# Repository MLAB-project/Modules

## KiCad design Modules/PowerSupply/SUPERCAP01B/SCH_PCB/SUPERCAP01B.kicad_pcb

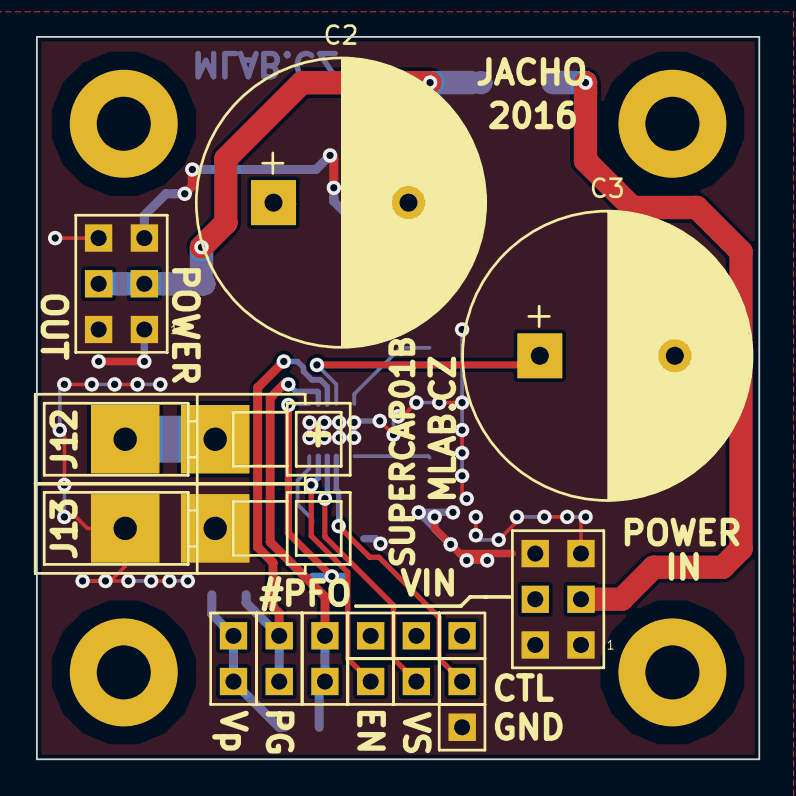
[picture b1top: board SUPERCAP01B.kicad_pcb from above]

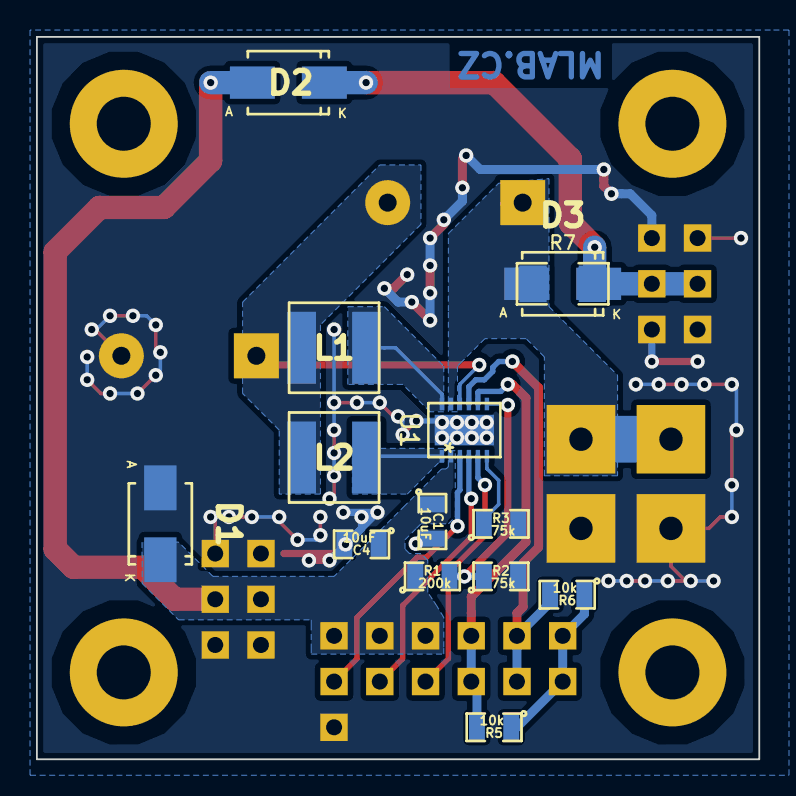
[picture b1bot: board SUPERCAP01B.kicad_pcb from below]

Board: 2 copper layers, 40.1 x 40.1 mm, 34 parts (14 on the bottom side), 15 nets.

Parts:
C1, C4: 10uF; SMD-0805
C2, C3: 22F; C_Radial_D16_L25_P7.5
D1: M4; SMA_Standard
D2, D3: 15MQ040N; Diode-SMA_Standard
J1, J11: JUMP_3X2; Straight_2x03
J2, J3, J4, J5, J6, J7, J8: CONN1_1; Straight_1x01
J9, J10, J14: JUMP_2x1; Straight_2x01
J12, J13: CONN1_1; WAGO256
L1, L2: DJNR5040-3R3-S; DJNR5040
M1, M2, M3, M4: HOLE; MountingHole_3mm
R1: 200k; SMD-0805
R2, R3: 75k; SMD-0805
R5, R6: 10k; SMD-0805
R7: 0R; SMD-1206
U1: LTC3625; DFN-12-1EP_3x4mm_Pitch0.5mm

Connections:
/#PFO: J9.1, J9.2, R5.2, U1.8
/CTL: J3.1, U1.3
/EN: J6.1, U1.5
/OUT: C2.1, D3.2, J12.1, R7.2, U1.11
/OUT2: D2.1, D3.1, J11.3, J11.4, R7.1
/PG: J10.1, J10.2, R6.2, U1.9
/VIN: C1.1, C4.1, D1.1, D2.2, J1.3, J1.4, J2.1, J5.1, J7.1, R1.1, U1.2
/VSEL: J8.1, U1.4
/Vpull-up: J14.1, J14.2, R5.1, R6.1
GND: C1.2, C3.2, C4.2, D1.2, J1.1, J1.2, J1.5, J1.6, J4.1, J11.1, J11.2, J11.5, J11.6, J13.1, R2.2, R3.2, U1.13
unnamed: C2.2, C3.1, L1.2, L2.2, U1.10
unnamed: L1.1, U1.12
unnamed: L2.1, U1.1
unnamed: R1.2, R2.1, U1.7
unnamed: R3.1, U1.6

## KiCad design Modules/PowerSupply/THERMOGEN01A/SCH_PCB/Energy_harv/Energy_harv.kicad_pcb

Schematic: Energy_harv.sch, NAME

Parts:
C1, C10: 47uF; TantalC_SizeC_Reflow
C2, C4: 1nF; SMD-0805
C3, C5: 470pF; SMD-0805
C6: 1uF; SMD-0805
C7: 2,2uF; SMD-0805
C8: 470uF; TantalC_SizeD_Reflow
C9: 1-10F; Straight_1x02
J1, J2: JUMP1X3; Straight_1x03
J3, J4: JUMP1X2; Straight_1x02
J5, J6: JUMP2X3; Straight_2x03
M1, M2, M3, M4: HOLE; MountingHole_3mm
P1, P2, P3, P4: WAGO256
T1, T2: Step-Up_TRANSFO; Step-Up_TRANSF
U1: THERM_GEN; Straight_1x02
U2: LTC3109GN; SSOP-20

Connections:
/C+: C9.1, P4.1, U2.3 (VSTORE)
/PGOOD: J4.1, J4.2, U2.8 (PGOOD)
/T+: C1.1, P1.1, T1.1 (AA), U1.2, U2.15 (V_INB)
/T-: C1.2, P2.1, T2.1 (AA), U1.1, U2.16 (V_INA)
/VAUX: C6.1, J1.3, J2.3, U2.4 (VAUX)
/VOUT2_EN: J3.1, J3.2, U2.7 (V_OUT2_EN)
/VS1: J1.2, U2.1 (VS1)
/VS2: J2.2, U2.2 (VS2)
/V_OUT: C8.1, J6.3, J6.4, U2.5 (V_OUT)
/V_OUT2: C10.1, J5.3, J5.4, U2.6 (V_OUT2)
GND: C6.2, C7.2, C8.2, C9.2, C10.2, J1.1, J2.1, J5.1, J5.2, J5.5, J5.6, J6.1, J6.2, J6.5, J6.6, P3.1, T1.3 (SA), T2.3 (SA), U2.10 (GND), U2.13 (GND), U2.18 (GND)
unnamed: C2.1, U2.20 (C1A)
unnamed: C2.2, C3.2, T1.4 (SB)
unnamed: C3.1, U2.19 (C2A)
unnamed: C4.1, U2.11 (C1B)
unnamed: C4.2, C5.2, T2.4 (SB)
unnamed: C5.1, U2.12 (C2B)
unnamed: C7.1, U2.9 (VLDO)
unnamed: T1.2 (AB), U2.17 (SWA)
unnamed: T2.2 (AB), U2.14 (SWB)

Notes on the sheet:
V_out2
V_out

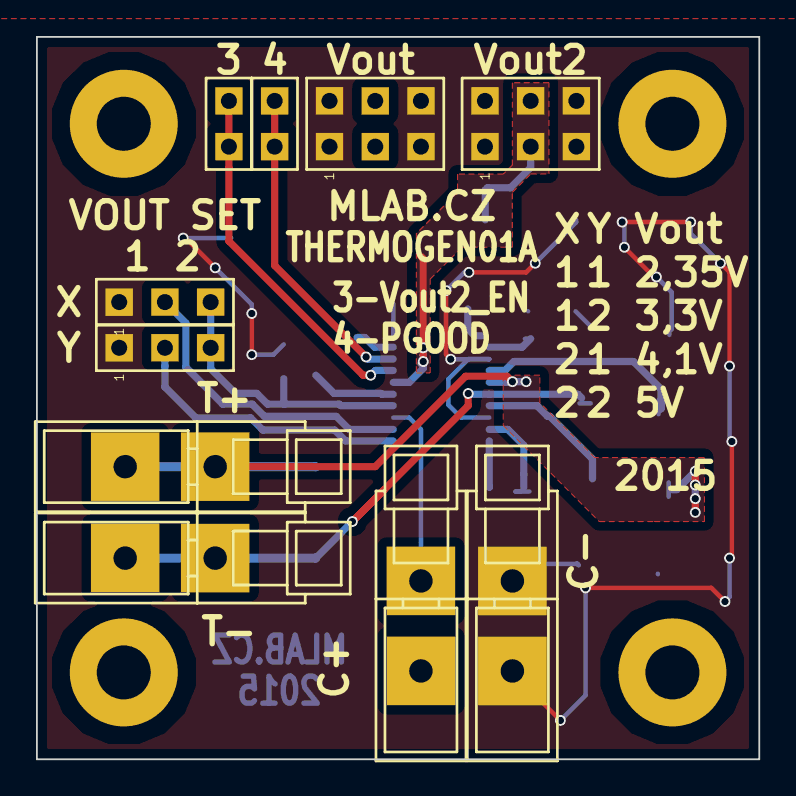
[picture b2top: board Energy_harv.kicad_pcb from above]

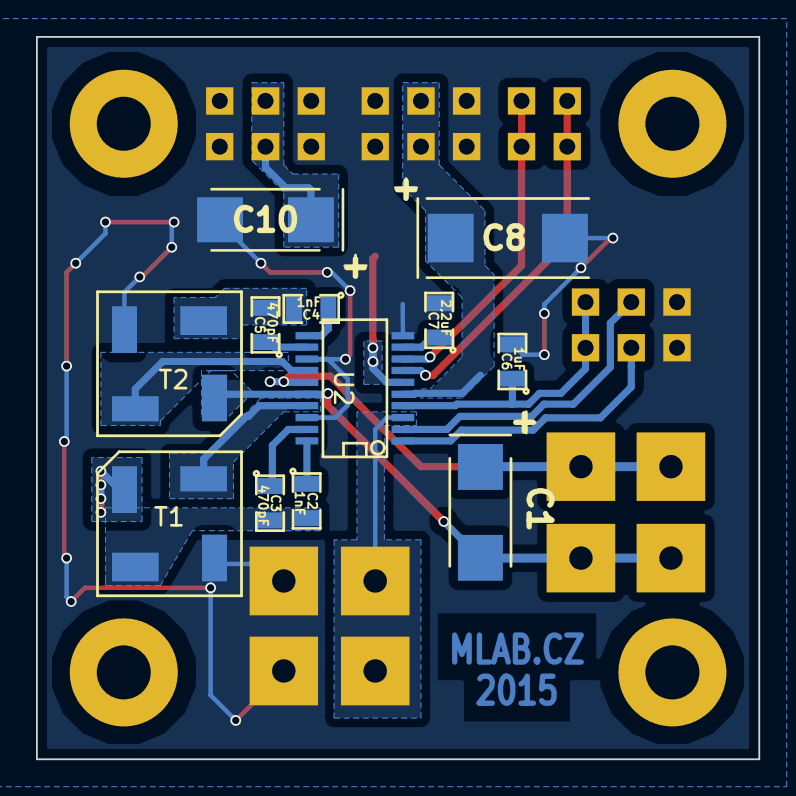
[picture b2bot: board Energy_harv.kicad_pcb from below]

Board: 2 copper layers, 40.1 x 40.1 mm, 26 parts (12 on the bottom side), 20 nets.

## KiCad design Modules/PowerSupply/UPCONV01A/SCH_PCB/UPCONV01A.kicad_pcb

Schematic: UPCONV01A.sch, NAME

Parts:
C1: 470uF; TantalC_SizeD_Reflow
C2, C6: 100nF; SMD-0805
C3: 10uF/16V; SMD-0805
C5, C7: 220uF; TantalC_SizeD_Reflow
C9: 10uF; SMD-0805
C10: 2.2nF; SMD-0805
C11: 47pF; SMD-0805
C12: 10nF; SMD-0805
C13: 100pF; SMD-0805
C14: 10uF/25V; SMD-0805
C15: 470pF; SMD-0805
C21: 470uF/35V; C_Radial_D10_L13_P5
D1: M4; Diode-SMA_Standard
D2, D3: STPS340U; Diode-SMB_Standard
J1, J2, J3, J7, J8, J9, J10, J11, J12: JUMP_2x1; Straight_1x02
J4, J5, J6: JUMP2_2x1; Straight_1x02
L1: DE1207-10, EPCOS B82477G4682M; DE1205-10
L2: BLM21PG300SN1; SMD-0805
M1, M2, M3, M4: HOLE; MountingHole_3mm
P1, P2, P3, P4: WAGO256
R1: 51k; SMD-0805
R2, R4: 10k; SMD-0805
R3: 84k5; SMD-0805
R5: 28k7; SMD-0805
R6: -; SMD-0805
R7: 499R; SMD-0805
U1: PAM2423; SOP-8_EP_3.9x4.9mm_Pitch1.27mm

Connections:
/5V: J5.1, R5.1
/12V: J4.1, R4.1
/ADJ: J6.1, R6.1
/EN: J2.1, J2.2, R2.2, U1.3 (EN)
/Vout: C5.1, C7.1, C13.1, C14.1, C21.1, D2.1 (K), D3.1 (K), L2.1, P3.1, R7.1
GND: C1.2, C2.2, C3.2, C5.2, C6.2, C7.2, C9.2, C10.2, C11.2, C12.2, C14.2, C15.2, C21.2, D1.2 (A), J1.1, J1.2, J3.1, J3.2, J7.1, J7.2, J10.1, J10.2, J12.1, J12.2, P2.1, P4.1, R4.2, R5.2, R6.2, U1.1 (PGND), U1.5 (AGND), U1.9 (GND)
unnamed: C6.1, J8.1, J8.2, J9.1, J9.2, L2.2
unnamed: C10.1, R1.2
unnamed: C11.1, R1.1, U1.4 (COMP)
unnamed: C12.1, U1.7 (SS)
unnamed: C13.2, C15.1, J4.2, J5.2, J6.2, R3.2, U1.6 (FB)
unnamed: D2.2 (A), D3.2 (A), L1.2, U1.8 (SW)
unnamed: R3.1, R7.2
VCC: C1.1, C2.1, C3.1, C9.1, D1.1 (K), J11.1, J11.2, L1.1, P1.1, R2.1, U1.2 (VIN)

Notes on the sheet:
POWER INPUT
MOUNTING HOLES
POWER OUT

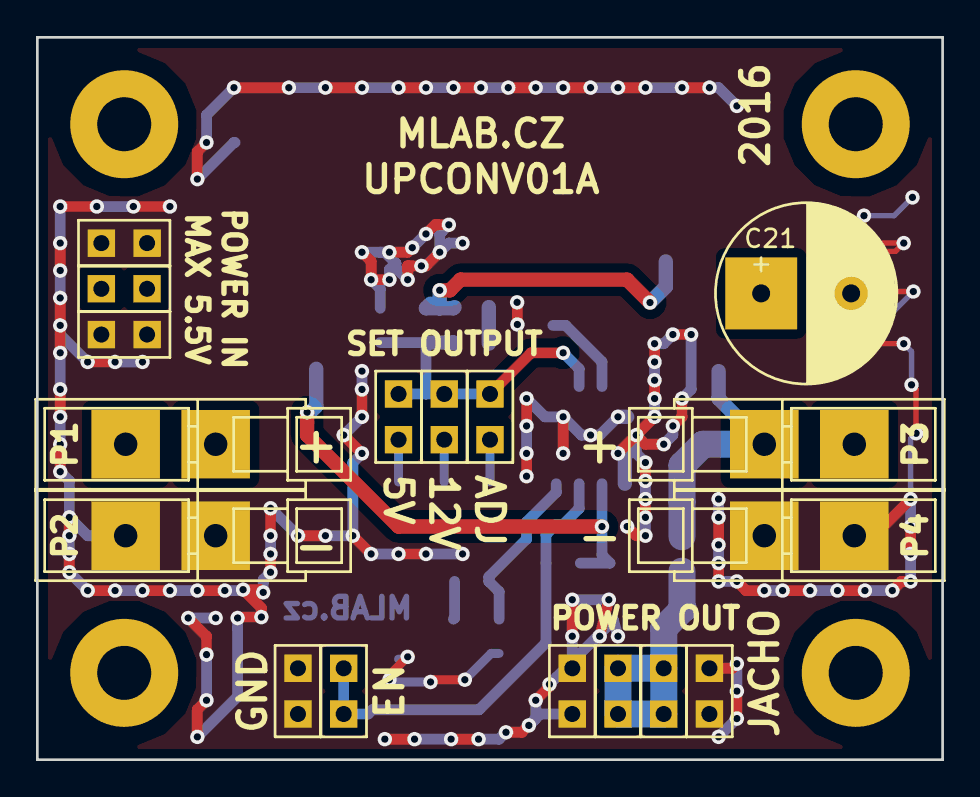
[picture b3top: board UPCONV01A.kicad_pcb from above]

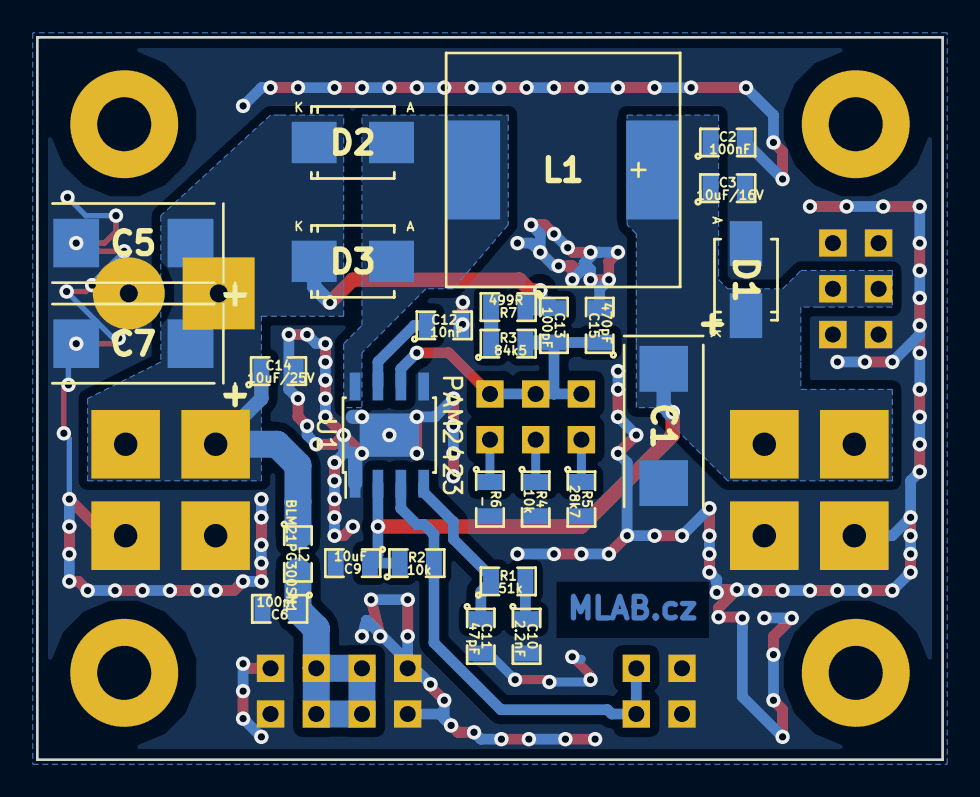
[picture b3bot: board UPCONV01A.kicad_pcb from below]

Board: 2 copper layers, 50.3 x 40.1 mm, 47 parts (26 on the bottom side), 14 nets.

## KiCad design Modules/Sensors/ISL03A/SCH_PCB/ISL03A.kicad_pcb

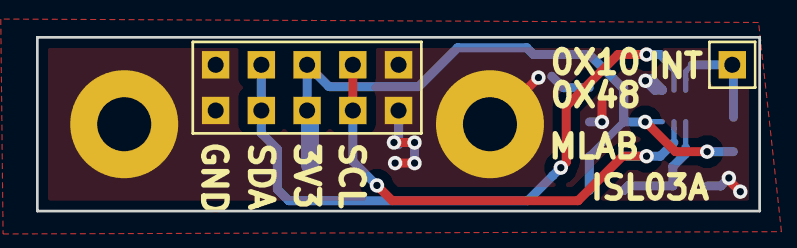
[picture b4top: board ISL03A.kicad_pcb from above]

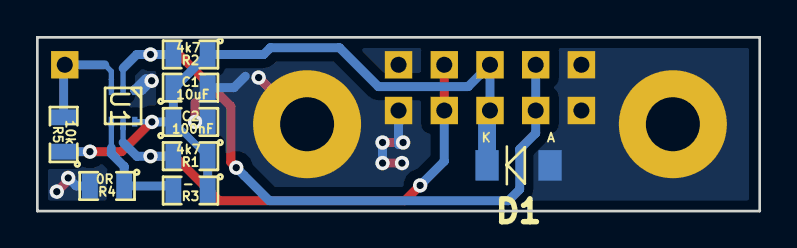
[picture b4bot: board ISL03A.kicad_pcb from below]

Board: 2 copper layers, 40.1 x 9.7 mm, 13 parts (9 on the bottom side), 6 nets.

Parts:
C1: 10uF; SMD-0805
C2: 100nF; SMD-0805
D1: BZV55C-3,6V; Diode-MiniMELF_Standard
J1: JUMP_5X2; Straight_2x05
J2: CONN1_1; Straight_1x01
M1, M2: HOLE; MountingHole_3mm
R1, R2: 4k7; SMD-0805
R3: -; SMD-0805
R4: 0R; SMD-0805
R5: 10k; SMD-0805
U1: VEML6030

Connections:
+3V3: C1.1, C2.1, D1.2, J1.5, J1.6, R1.1, R2.1, R3.1, R5.1, U1.6
/INT: J2.1, R5.2, U1.3
/SCL: J1.7, J1.8, R1.2, U1.5
/SDA: J1.3, J1.4, R2.2, U1.2
GND: C1.2, C2.2, D1.1, J1.1, J1.2, J1.9, J1.10, M1.1, M2.1, R4.2, U1.1
unnamed: R3.2, R4.1, U1.4

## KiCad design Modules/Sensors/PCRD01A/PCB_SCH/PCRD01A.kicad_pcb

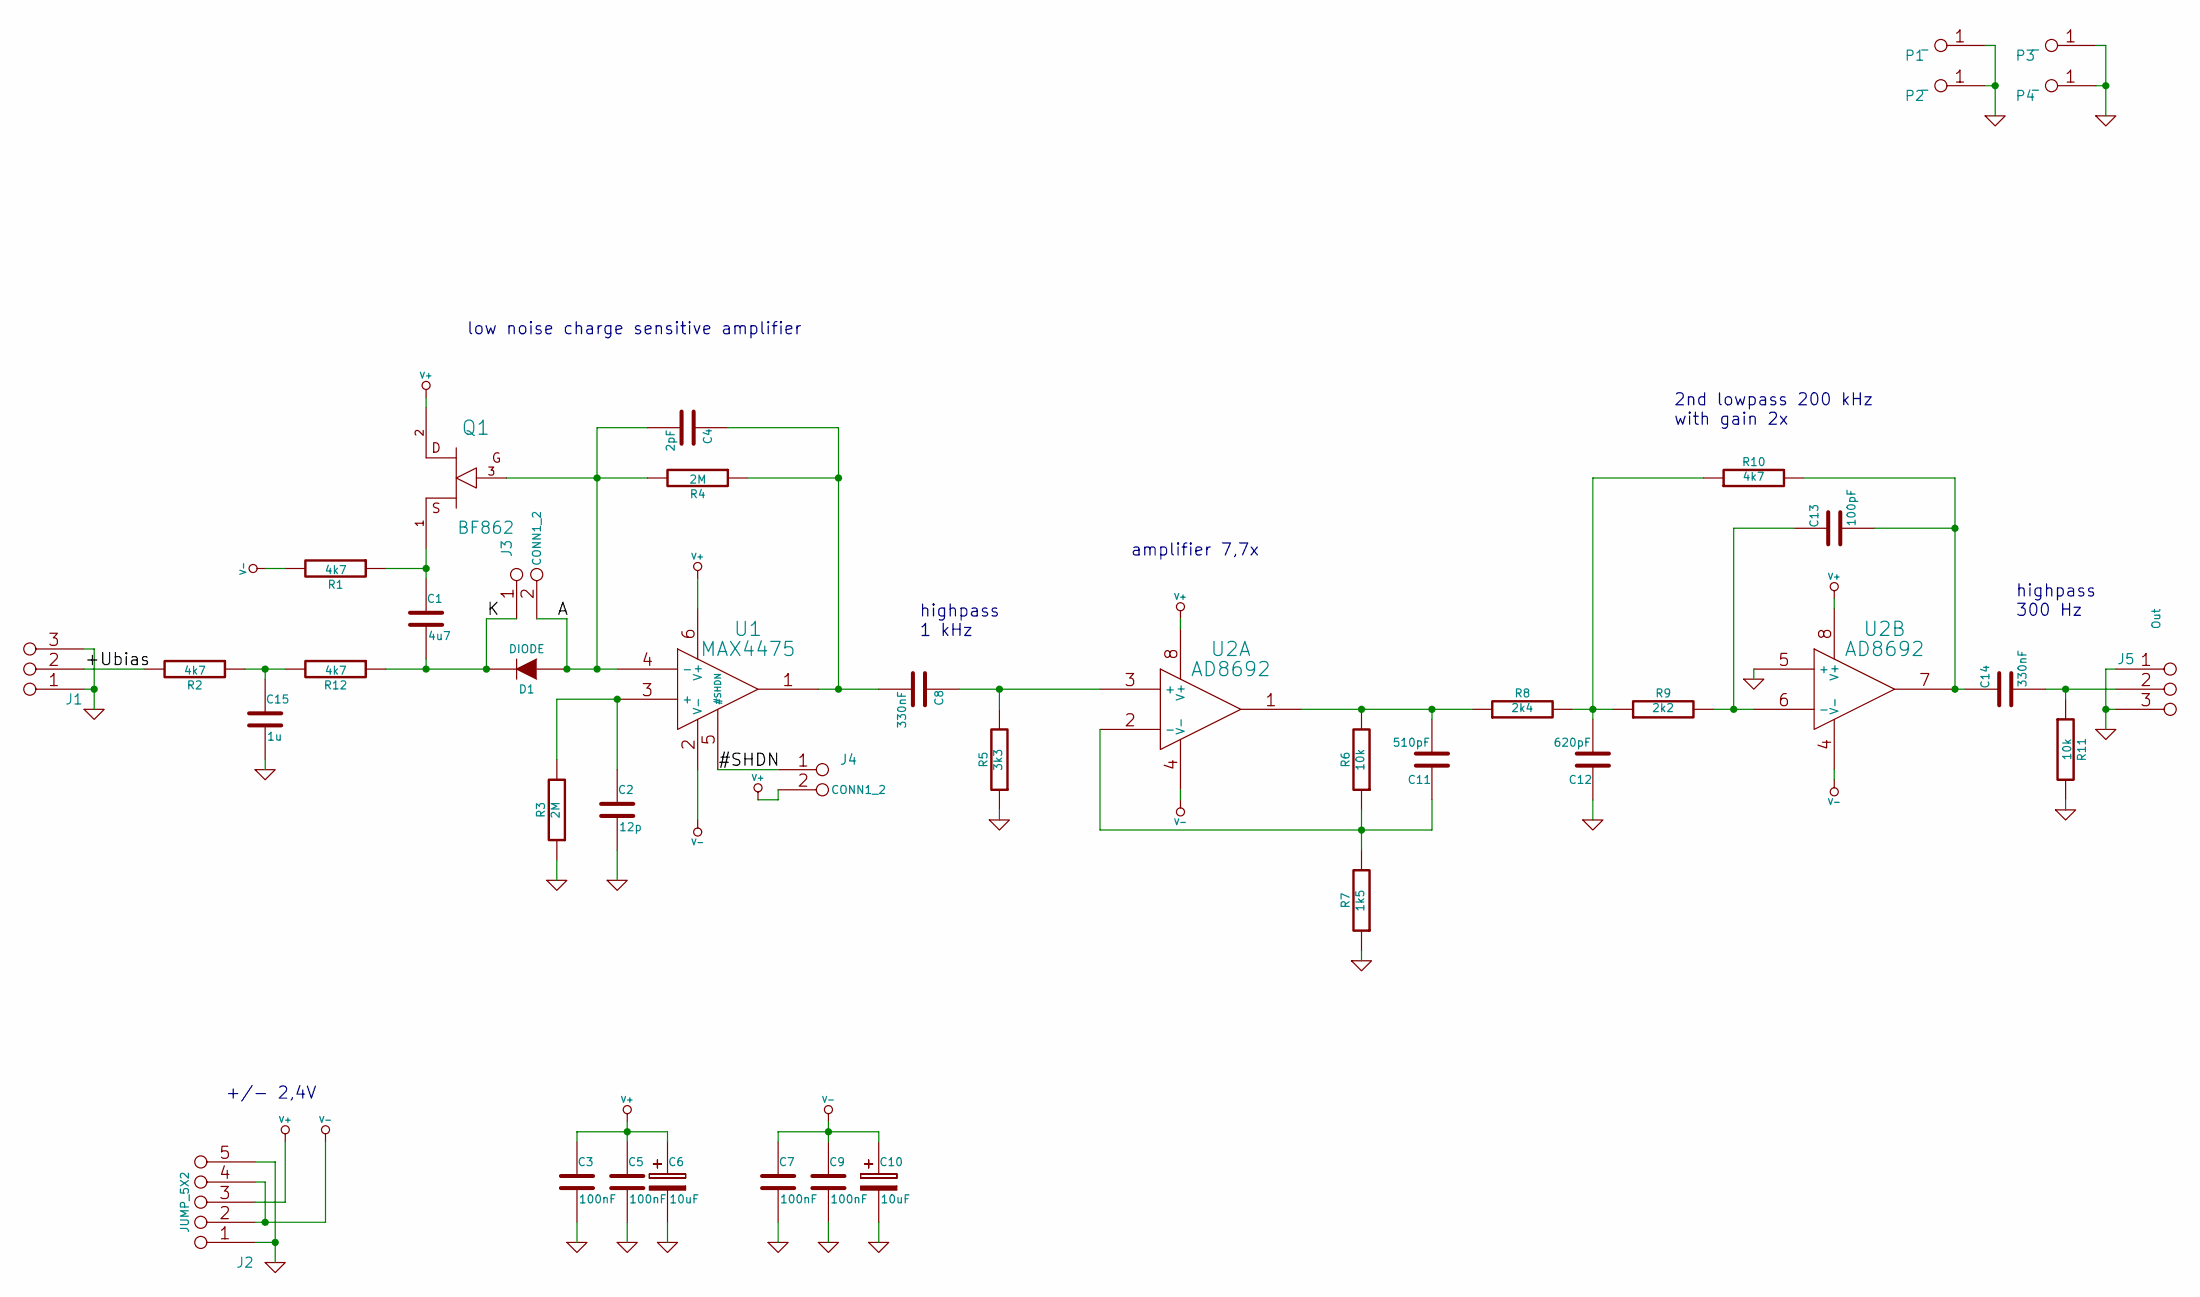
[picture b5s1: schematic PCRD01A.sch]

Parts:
C1: 4u7; SMD-0805
C2: 12p; SMD-0805
C3, C5, C7, C9: 100nF; SMD-0805
C4: 2pF; SMD-0805
C6, C10: 10uF; SMD-0805
C8, C14: 330nF; SMD-0805
C11: 510pF; SMD-0805
C12: 620pF; SMD-0805
C13: 100pF; SMD-0805
C15: 1u; SMD-0805
D1: DIODE
J1: JUMP_3X2; Pin_Header_Straight_2x03
J2: JUMP_5X2; Pin_Header_Straight_2x05
J3: CONN1_2; CONN_3_2
J4: CONN1_2; Pin_Header_Straight_1x02
J5: Out; Pin_Header_Straight_2x03
P1, P2, P3, P4: _; MountingHole_3mm
Q1: BF862; SOT-23
R1, R2, R10, R12: 4k7; SMD-0805
R3, R4: 2M; SMD-0805
R5: 3k3; SMD-0805
R6, R11: 10k; SMD-0805
R7: 1k5; SMD-0805
R8: 2k4; SMD-0805
R9: 2k2; SMD-0805
U1: MAX4475; SOT-23-6
U2: AD8692; SOIC-8-N

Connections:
/#SHDN: J4.1, U1.5 (#SHDN)
/+Ubias: J1.2 (1), J1.5, R2.2
/A: C4.2, D1.1 (A), J3.2 (PM), Q1.3 (G), R4.2, U1.4 (-)
/K: C1.2, D1.2 (K), J3.1, R12.1
GND: C2.2, C3.2, C5.2, C6.2, C7.2, C9.2, C10.2, C12.1, C15.2, J1.1, J1.3, J1.4, J1.6, J2.1, J2.5, J2.6, J2.10, J5.1, J5.3, J5.4, J5.6, P1.1, P2.1, P3.1, P4.1, R3.1, R5.1, R7.1, R11.2, U2.5 (+)
unnamed: C1.1, Q1.1 (S), R1.1
unnamed: C2.1, R3.2, U1.3 (+)
unnamed: C4.1, C8.2, R4.1, U1.1
unnamed: C8.1, R5.2, U2.3 (+)
unnamed: C11.1, R6.1, R7.2, U2.2 (-)
unnamed: C11.2, R6.2, R8.1, U2.1
unnamed: C12.2, R8.2, R9.1, R10.1
unnamed: C13.1, R9.2, U2.6 (-)
unnamed: C13.2, C14.1, R10.2, U2.7
unnamed: C14.2, J5.2 (1), J5.5, R11.1
unnamed: C15.1, R2.1, R12.2
V+: C3.1, C5.1, C6.1, J2.3, J2.8, J4.2 (PM), Q1.2 (D), U1.6 (V+), U2.8 (V+)
V-: C7.1, C9.1, C10.1, J2.2, J2.4, J2.7, J2.9, R1.2, U1.2 (V-), U2.4 (V-)

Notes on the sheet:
low noise charge sensitive amplifier
highpass 1 kHz
amplifier 7,7x
2nd lowpass 200 kHz with gain 2x
highpass 300 Hz
+/- 2,4V

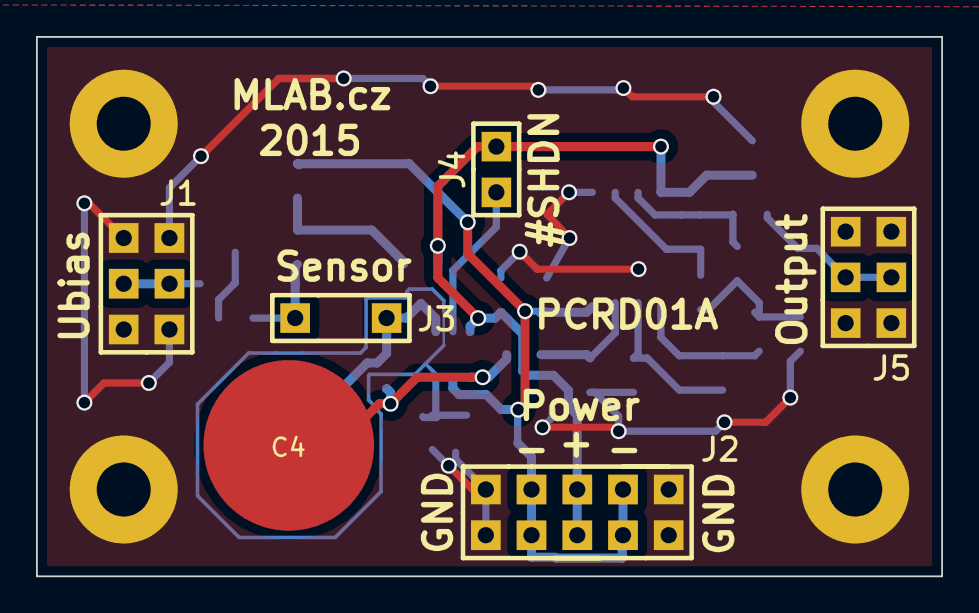
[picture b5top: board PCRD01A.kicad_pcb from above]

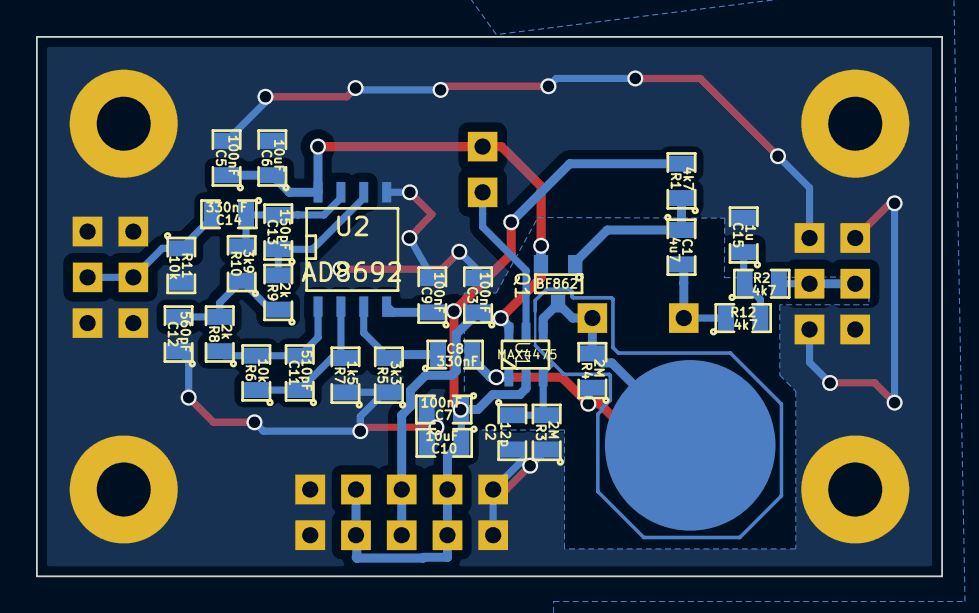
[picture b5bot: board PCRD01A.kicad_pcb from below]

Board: 2 copper layers, 50.3 x 30.0 mm, 39 parts (29 on the bottom side), 18 nets.

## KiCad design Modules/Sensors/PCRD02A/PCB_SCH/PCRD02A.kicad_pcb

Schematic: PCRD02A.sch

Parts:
C1, C2: 100nF; SMD-0805
C3, C4, C9, C10, C11: 100n; SMD-0805
C5, C8: 2pF; C2pF
C13, C17: 330nF; SMD-0805
C14: 510pF; SMD-0805
C15: 240pF; SMD-0805
C16: 180pF; SMD-0805
D1: DIODE
J1: CONN1_2; CONN_3_2
J2: JUMP_3X2; Pin_Header_Straight_2x03
J3: JUMP_5X2; Pin_Header_Straight_2x05
J4: Out; Pin_Header_Straight_2x03
P1, P2, P3, P4: _; MountingHole_3mm
Q1: BF862; SOT-23
R1, R2: 4M7; SMD-0805
R3, R4, R5, R6: R; SMD-0805
R7: 2M; SMD-0805
R8: 3k3; SMD-0805
R9, R15: 10k; SMD-0805
R10: 1k5; SMD-0805
R11: 3k9; SMD-0805
R12, R13, R14: 2k4; SMD-0805
U1: AD8691; tsot-5
U2: AD8692; SOIC-8-N

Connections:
GND: C1.2, C3.2, C4.2, C9.2, C10.2, C11.2, C15.2, D1.1 (A), J1.1, J2.1, J2.3, J2.4, J2.6, J3.1, J3.5, J3.6, J3.10, J4.1, J4.3, J4.4, J4.6, P1.1, P2.1, P3.1, P4.1, R8.2, R10.2, R13.2, R15.2
unnamed: C1.1, R1.2, R2.1
unnamed: C2.1, C8.2, Q1.3 (G), R7.2
unnamed: C2.2, D1.2 (K), J1.2 (PM), R2.2
unnamed: C5.1, R5.2, R6.1, U1.4 (-)
unnamed: C13.1, R8.1, U2.3
unnamed: C8.1, C13.2, R7.1, U1.1
unnamed: C14.1, R9.2, R10.1, U2.2
unnamed: C14.2, R9.1, R11.2, U2.1
unnamed: C15.1, R12.1, U2.5
unnamed: C16.1, C17.2, R14.1, U2.7
unnamed: C16.2, R11.1, R12.2
unnamed: C17.1, J4.2 (1), J4.5, R15.1
unnamed: J2.2 (1), J2.5, R1.1
unnamed: Q1.2 (D), R4.2, U1.3 (+)
unnamed: R3.2, R4.1, R5.1
unnamed: R13.1, R14.2, U2.6
V+: C3.1, C4.1, J3.3, J3.8, R3.1, U1.5 (V+), U2.8
V-: C5.2, C9.1, C10.1, C11.1, J3.2, J3.4, J3.7, J3.9, Q1.1 (S), R6.2, U1.2 (V-), U2.4

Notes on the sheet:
low noise charge sensitive amplifier
highpass 1 kHz
amplifier 7,7x
2nd lowpass 200kHz with gain 2x
highpass 300 Hz
+/- 2,4 V

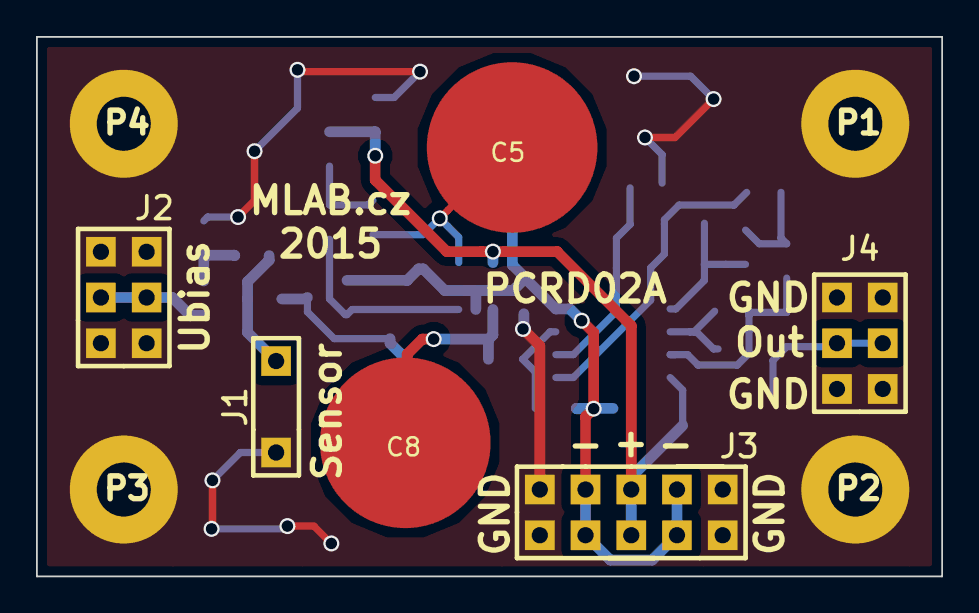
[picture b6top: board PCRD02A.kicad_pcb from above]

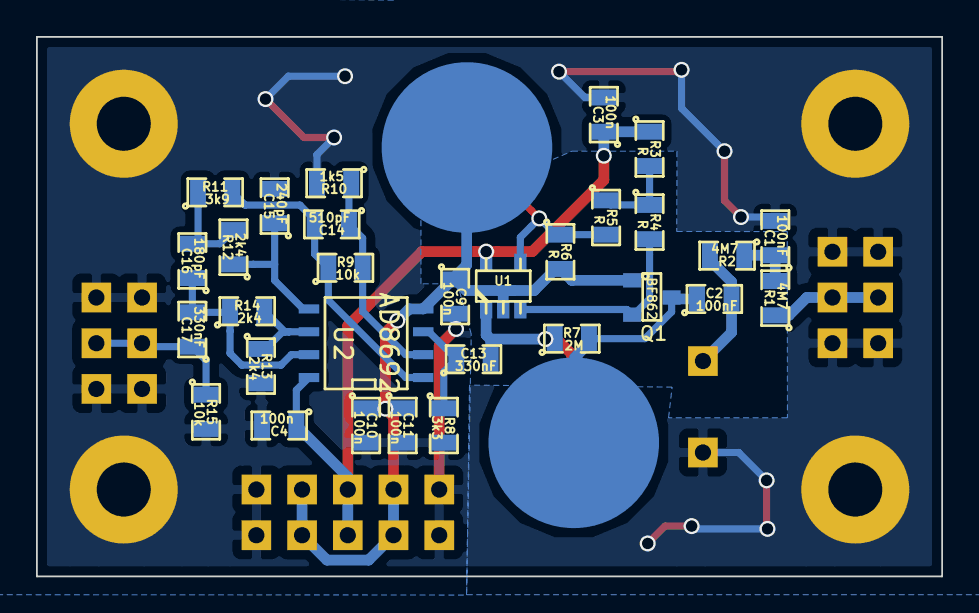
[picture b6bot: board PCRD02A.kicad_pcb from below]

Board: 2 copper layers, 50.3 x 30.0 mm, 40 parts (30 on the bottom side), 19 nets.

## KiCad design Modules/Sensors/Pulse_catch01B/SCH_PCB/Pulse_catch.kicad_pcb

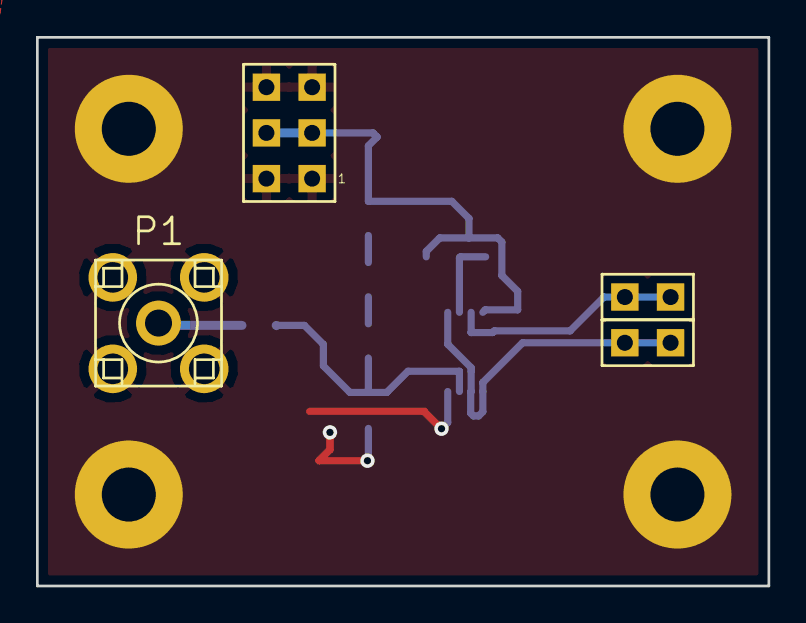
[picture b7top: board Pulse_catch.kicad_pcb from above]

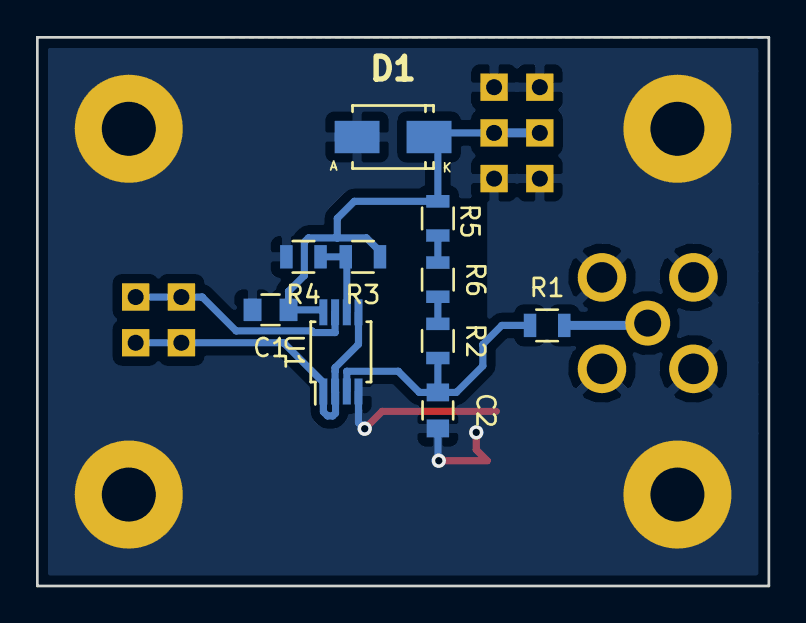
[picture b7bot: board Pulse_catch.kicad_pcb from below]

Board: 2 copper layers, 40.6 x 30.5 mm, 18 parts (10 on the bottom side), 9 nets.

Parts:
C1, C2: 100nF; C_0805
D1: D_Schottky; Diode-SMA_Standard
J1: HEADER_2x03_PARALLEL; Straight_2x03
J2: INTENSITY; Straight_1x02
J3: INT_OUT; Straight_1x02
M1, M2, M3, M4: HOLE; MountingHole_3mm
P1: SMA; SMA6251A13G50
R1: 10k; R_0805
R2, R4, R5, R6: 10M; R_0805
R3: 1M; R_0805
U1: MCP6002; MSOP-8_3x3mm_Pitch0.65mm

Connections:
GNDA: C1.2, C2.2, D1.2, J1.1, J1.2, J1.5, J1.6, M1.1, M2.1, M3.1, M4.1, P1.2, R4.2, U1.4
unnamed: C2.1, R1.1, R2.2, U1.3
unnamed: J2.1, J2.2, U1.1, U1.2, U1.5
unnamed: J3.1, J3.2, U1.7
unnamed: P1.1, R1.2
unnamed: R2.1, R6.2
unnamed: R3.2, R4.1, U1.6
unnamed: R5.2, R6.1
VDD: C1.1, D1.1, J1.3, J1.4, R3.1, R5.1, U1.8

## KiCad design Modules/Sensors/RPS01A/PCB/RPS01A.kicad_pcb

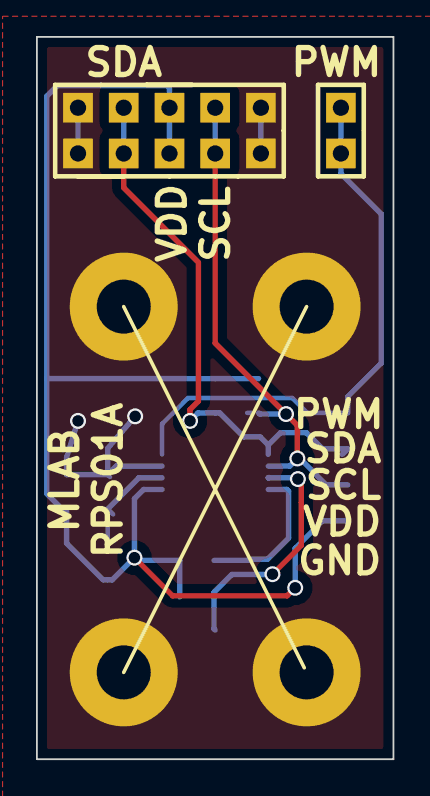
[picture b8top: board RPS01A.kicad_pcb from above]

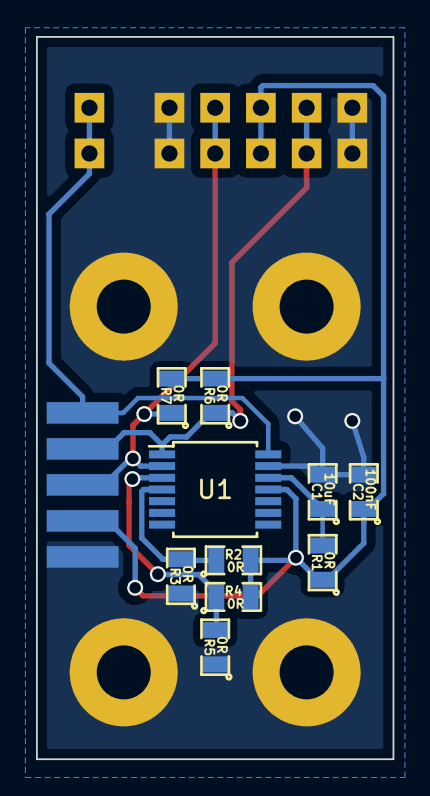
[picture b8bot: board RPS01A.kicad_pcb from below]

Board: 2 copper layers, 19.8 x 40.1 mm, 17 parts (11 on the bottom side), 8 nets.

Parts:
C1: 10uF; SMD-0805
C2: 100nF; SMD-0805
J1: JUMP_5X2; Pin_Header_Straight_2x05
J2: JUMP_2x1; Pin_Header_Straight_2x01
J3: JUMP_5X2; SMD_JUMP1X5
P1, P2, P3, P4: _; MountingHole_3mm
R1, R2, R3, R4, R5, R6, R7: 0R; SMD-0805
U1: AS5048B; TSSOP-14_4.4x5mm_Pitch0.65mm

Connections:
/A1: R2.1, R3.2, U1.4
/A2: R4.1, R5.2, U1.3
/PWM: J2.1, J2.2, J3.5, U1.14
/SCL: J1.2, J1.9, J3.3, R7.1, U1.2
/SDA: J1.4, J1.7, J3.4, R6.1, U1.1
GND: C1.2, C2.2, J1.1, J1.5, J1.6, J1.10, J3.1, P1.1, P2.1, P3.1, P4.1, R3.1, R5.1, U1.13
unnamed: C1.1, R1.2, U1.12
VDD: C2.1, J1.3, J1.8, J3.2, R1.1, R2.2, R4.2, R6.2, R7.2, U1.11
